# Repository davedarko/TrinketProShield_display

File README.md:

# TrinketProShield for bubble displays
Shield for trinket pro to feature a bubble display and lm75

I created this project, inspired by the events in Texas, 
where a 9th grade kid called Ahmed got arrested for bringing a clock as a hardware project to school.

It is a shield for an adafruit trinket pro, based on an atmega238p with vusb.

An additional temparature sensor in the form of the LM75 can be added to this bubble display shield.
The atmega32p is capable of driving up to 40mA per pin, so with the display needing 5mA per element of a digit,
it should be fine, since it will be a pulsed signal and there are 8 elements max.

The display is a famous poket calculator LED bubble display called the HP QDSP-6064.

For more details see:
http://hackaday.com/2015/09/16/why-you-should-build-a-clock-for-social-good-this-week/
https://hackaday.io/project/7690-trinket-pro-bubble-display-shield

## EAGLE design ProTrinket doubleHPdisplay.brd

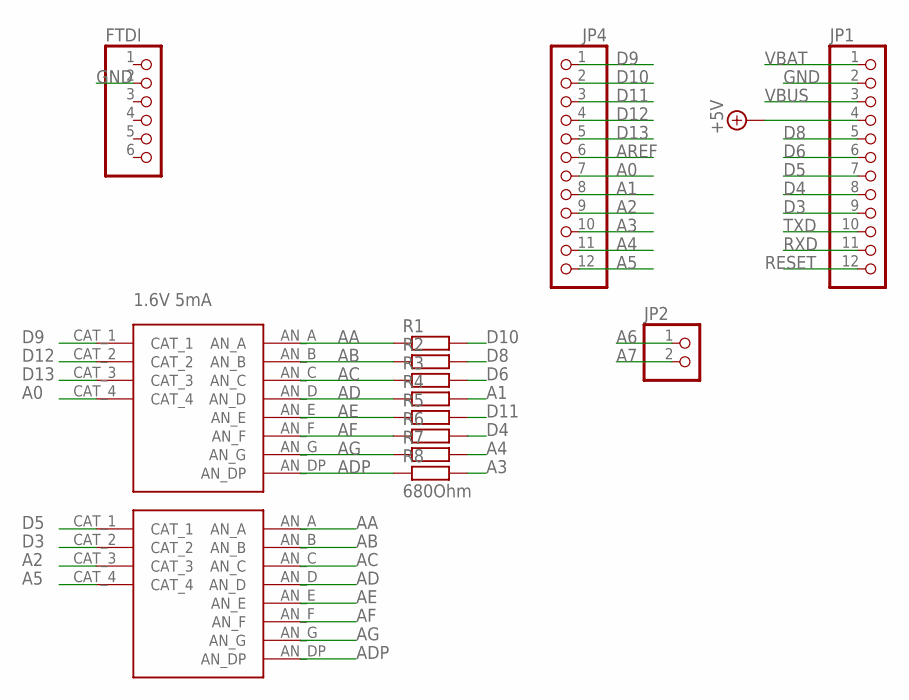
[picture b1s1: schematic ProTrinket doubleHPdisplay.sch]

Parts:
FTDI: PINHD-1X6CB; 1X06-CLEANBIG
JP1, JP4: PINHD-1X12-CB; 1X12-CB
JP2: HEADER-1X2ROUND; 1X02_ROUND
R1, R2, R3, R4, R5, R6, R7: R-EU_R0603; R0603
R8: 680Ohm; R0603
U$1, U$2: QDSP-6064

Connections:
+5V: JP1.4
A0: JP4.7, U$1.CAT_4
A1: JP4.8, R4.2
A2: JP4.9, U$2.CAT_3
A3: JP4.10, R8.2
A4: JP4.11, R7.2
A5: JP4.12, U$2.CAT_4
A6: JP2.1
A7: JP2.2
AA: R1.1, U$1.AN_A, U$2.AN_A
AB: R2.1, U$1.AN_B, U$2.AN_B
AC: R3.1, U$1.AN_C, U$2.AN_C
AD: R4.1, U$1.AN_D, U$2.AN_D
ADP: R8.1, U$1.AN_DP, U$2.AN_DP
AE: R5.1, U$1.AN_E, U$2.AN_E
AF: R6.1, U$1.AN_F, U$2.AN_F
AG: R7.1, U$1.AN_G, U$2.AN_G
AREF: JP4.6
D3: JP1.9, U$2.CAT_2
D4: JP1.8, R6.2
D5: JP1.7, U$2.CAT_1
D6: JP1.6, R3.2
D8: JP1.5, R2.2
D9: JP4.1, U$1.CAT_1
D10: JP4.2, R1.2
D11: JP4.3, R5.2
D12: JP4.4, U$1.CAT_2
D13: JP4.5, U$1.CAT_3
GND: FTDI.2, JP1.2
RESET: JP1.12
RXD: JP1.11
TXD: JP1.10
VBAT: JP1.1
VBUS: JP1.3

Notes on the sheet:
1.6V 5mA

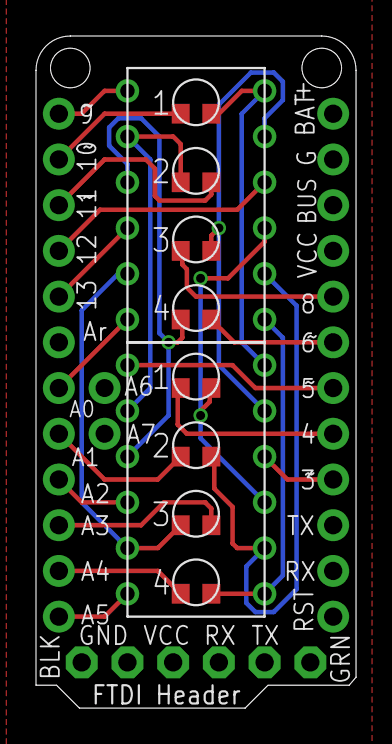
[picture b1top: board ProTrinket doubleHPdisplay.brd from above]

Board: 2 copper layers, 17.8 x 37.3 mm, 14 parts (0 on the bottom side), 25 nets.

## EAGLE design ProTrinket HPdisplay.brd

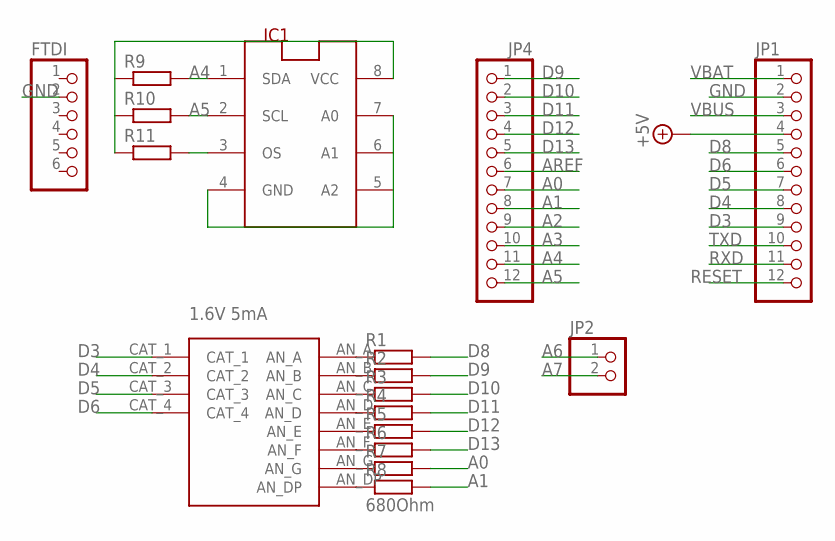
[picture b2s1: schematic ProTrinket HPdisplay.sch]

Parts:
FTDI: PINHD-1X6CB; 1X06-CLEANBIG
IC1: LM75_ICN; SO8_LM75
JP1, JP4: PINHD-1X12-CB; 1X12-CB
JP2: HEADER-1X2ROUND; 1X02_ROUND
R1, R2, R3, R4, R5, R6, R7: R-EU_R1206; R1206
R8: 680Ohm; R1206
R9, R10, R11: R-EU_R0603; R0603
U$1: QDSP-6064

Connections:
+5V: IC1.8 (VCC), JP1.4, R9.1, R10.1, R11.1
A0: JP4.7, R7.2
A1: JP4.8, R8.2
A2: JP4.9
A3: JP4.10
A4: IC1.1 (SDA), JP4.11, R9.2
A5: IC1.2 (SCL), JP4.12, R10.2
A6: JP2.1
A7: JP2.2
AREF: JP4.6
D3: JP1.9, U$1.CAT_1
D4: JP1.8, U$1.CAT_2
D5: JP1.7, U$1.CAT_3
D6: JP1.6, U$1.CAT_4
D8: JP1.5, R1.2
D9: JP4.1, R2.2
D10: JP4.2, R3.2
D11: JP4.3, R4.2
D12: JP4.4, R5.2
D13: JP4.5, R6.2
GND: FTDI.2, IC1.4 (GND), IC1.5 (A2), IC1.6 (A1), IC1.7 (A0), JP1.2
unnamed: R1.1, U$1.AN_A
unnamed: R2.1, U$1.AN_B
unnamed: R3.1, U$1.AN_C
unnamed: R4.1, U$1.AN_D
unnamed: R5.1, U$1.AN_E
unnamed: R6.1, U$1.AN_F
unnamed: R7.1, U$1.AN_G
unnamed: R8.1, U$1.AN_DP
unnamed: IC1.3 (OS), R11.2
RESET: JP1.12
RXD: JP1.11
TXD: JP1.10
VBAT: JP1.1
VBUS: JP1.3

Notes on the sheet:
1.6V 5mA

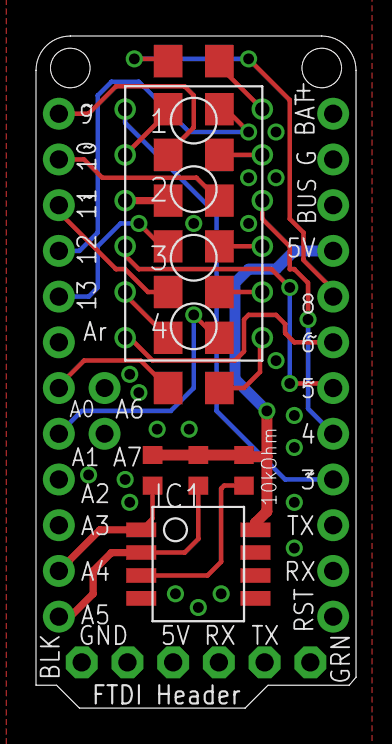
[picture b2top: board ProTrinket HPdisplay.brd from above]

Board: 2 copper layers, 17.8 x 37.3 mm, 17 parts (0 on the bottom side), 25 nets.

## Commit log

2015-09-17 init
2015-09-17 fixed IIC connection
2015-09-17 removed vias
2015-09-21 mixed up IIC lines
2015-09-21 dual display shield
2015-09-21 routed board (thx jaromir)
2016-11-17 gitignore

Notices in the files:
parts and their libraries:
microbuilder: This work is placed in the public domain, and may be freely used for commercial and non-commercial work with the following conditions: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
